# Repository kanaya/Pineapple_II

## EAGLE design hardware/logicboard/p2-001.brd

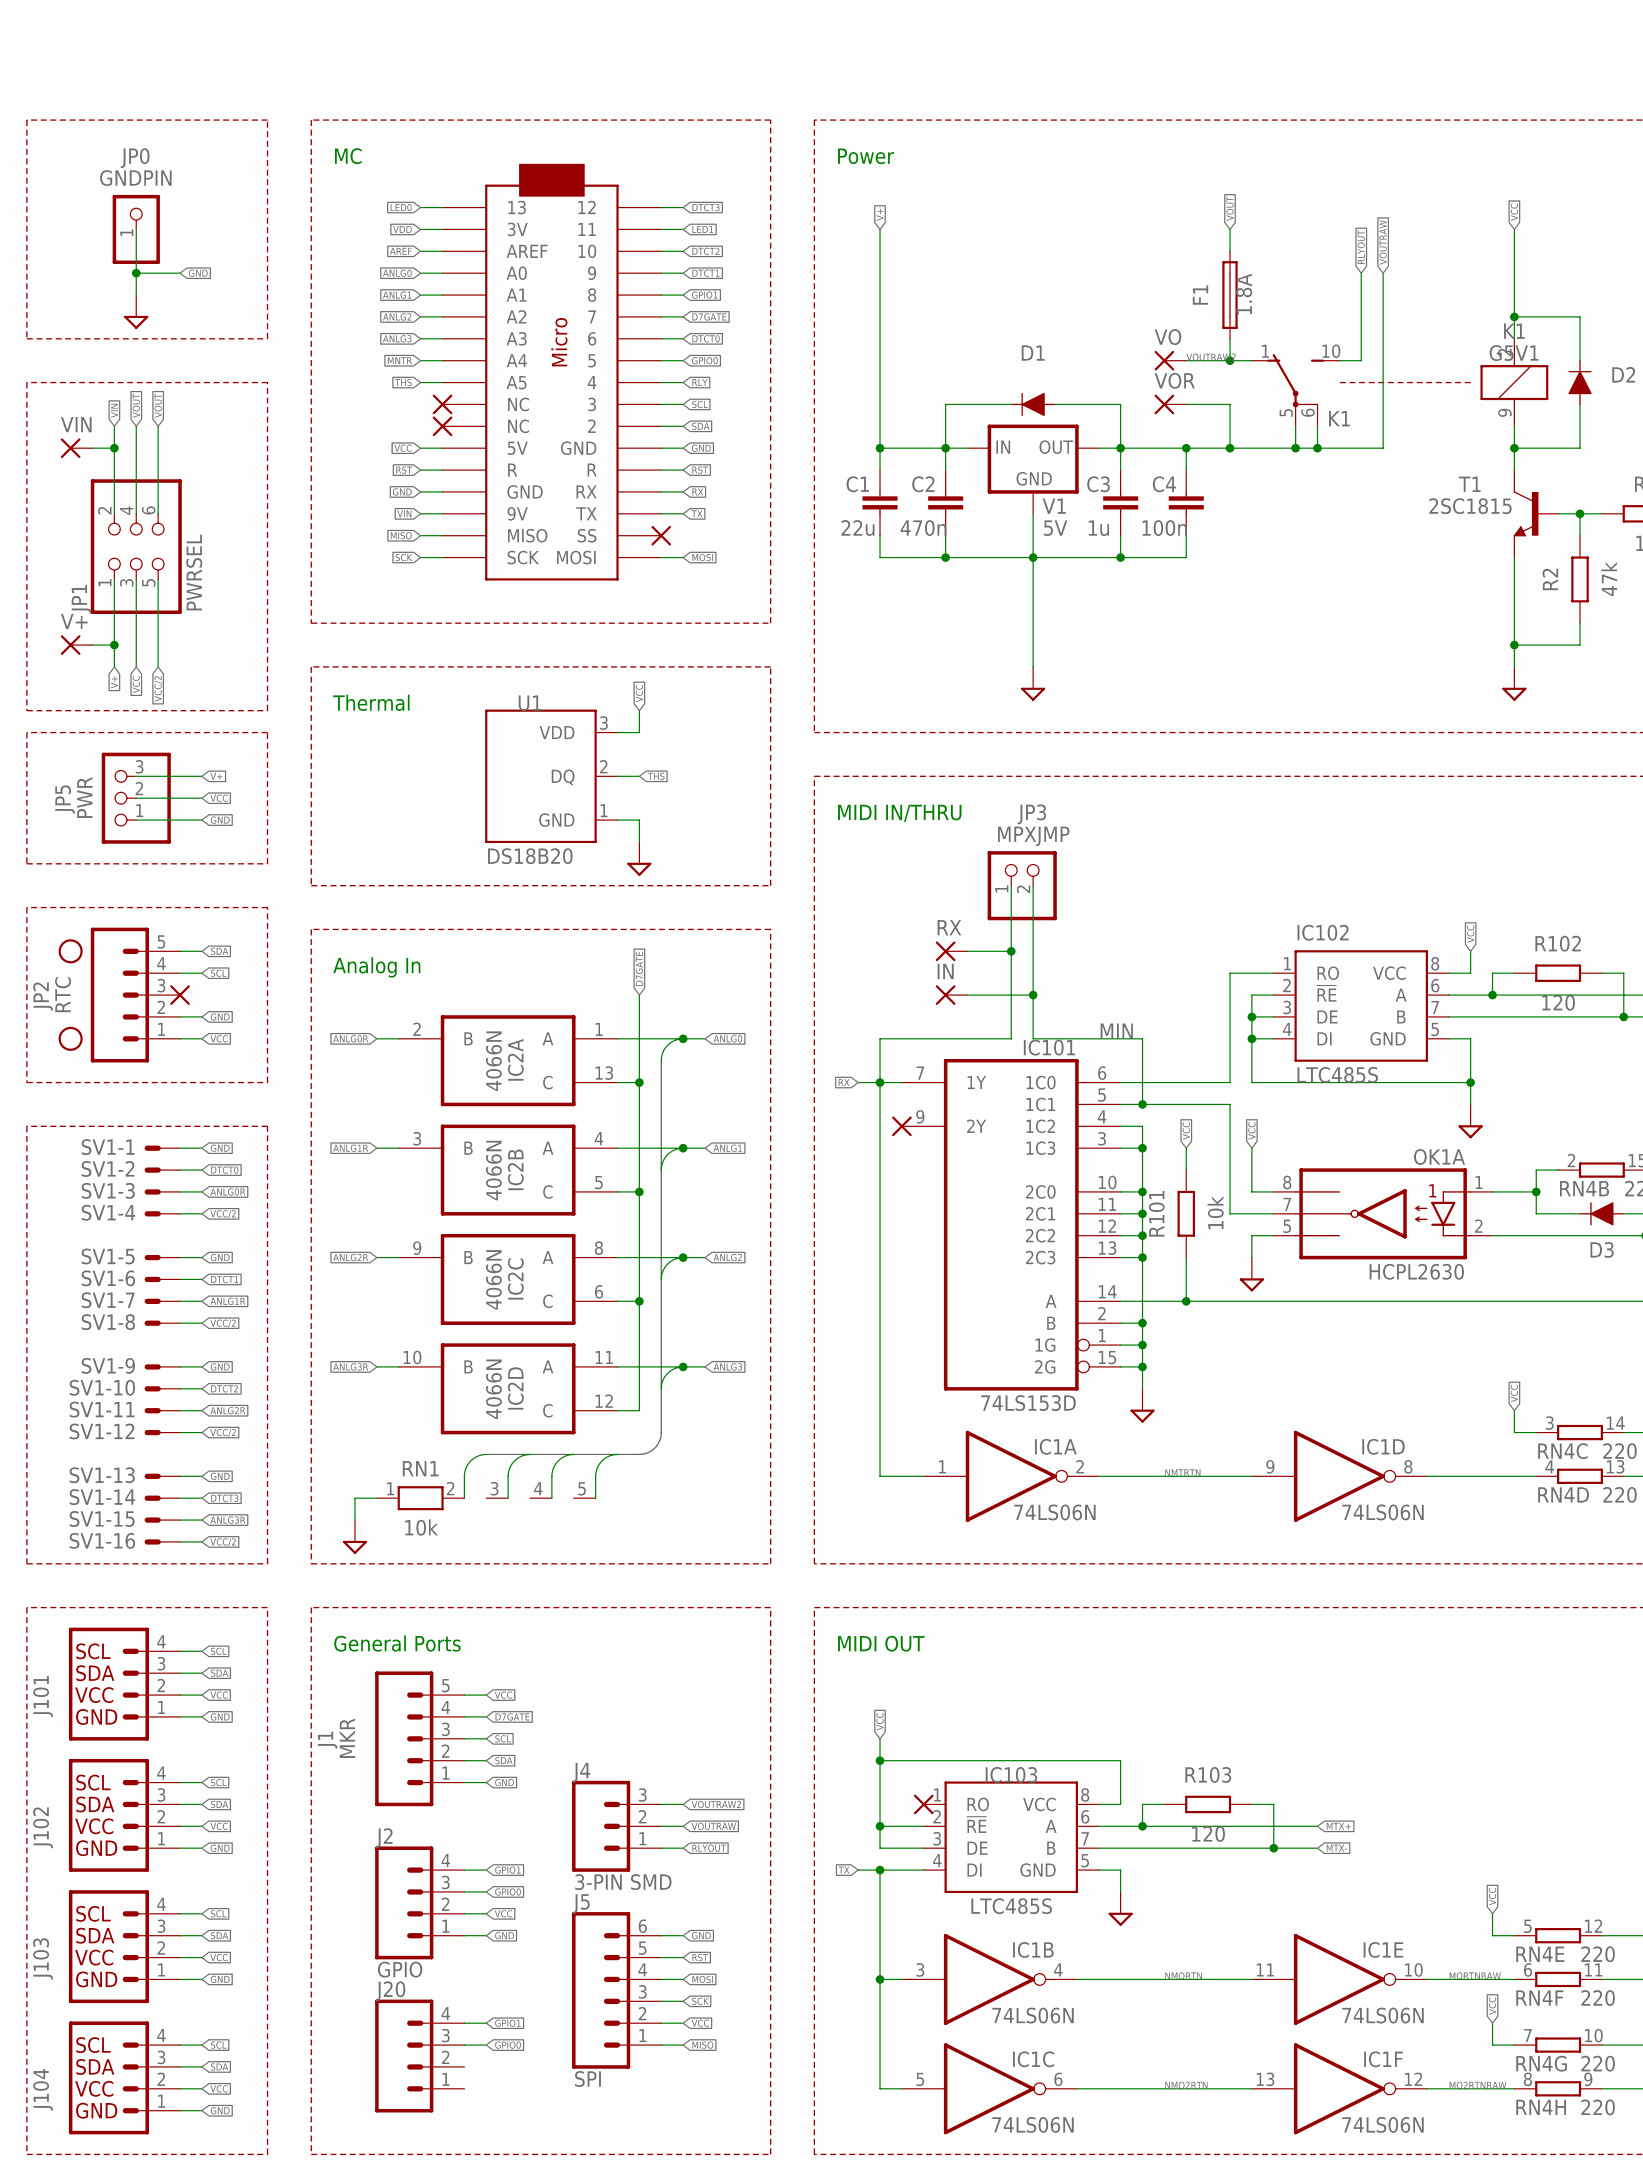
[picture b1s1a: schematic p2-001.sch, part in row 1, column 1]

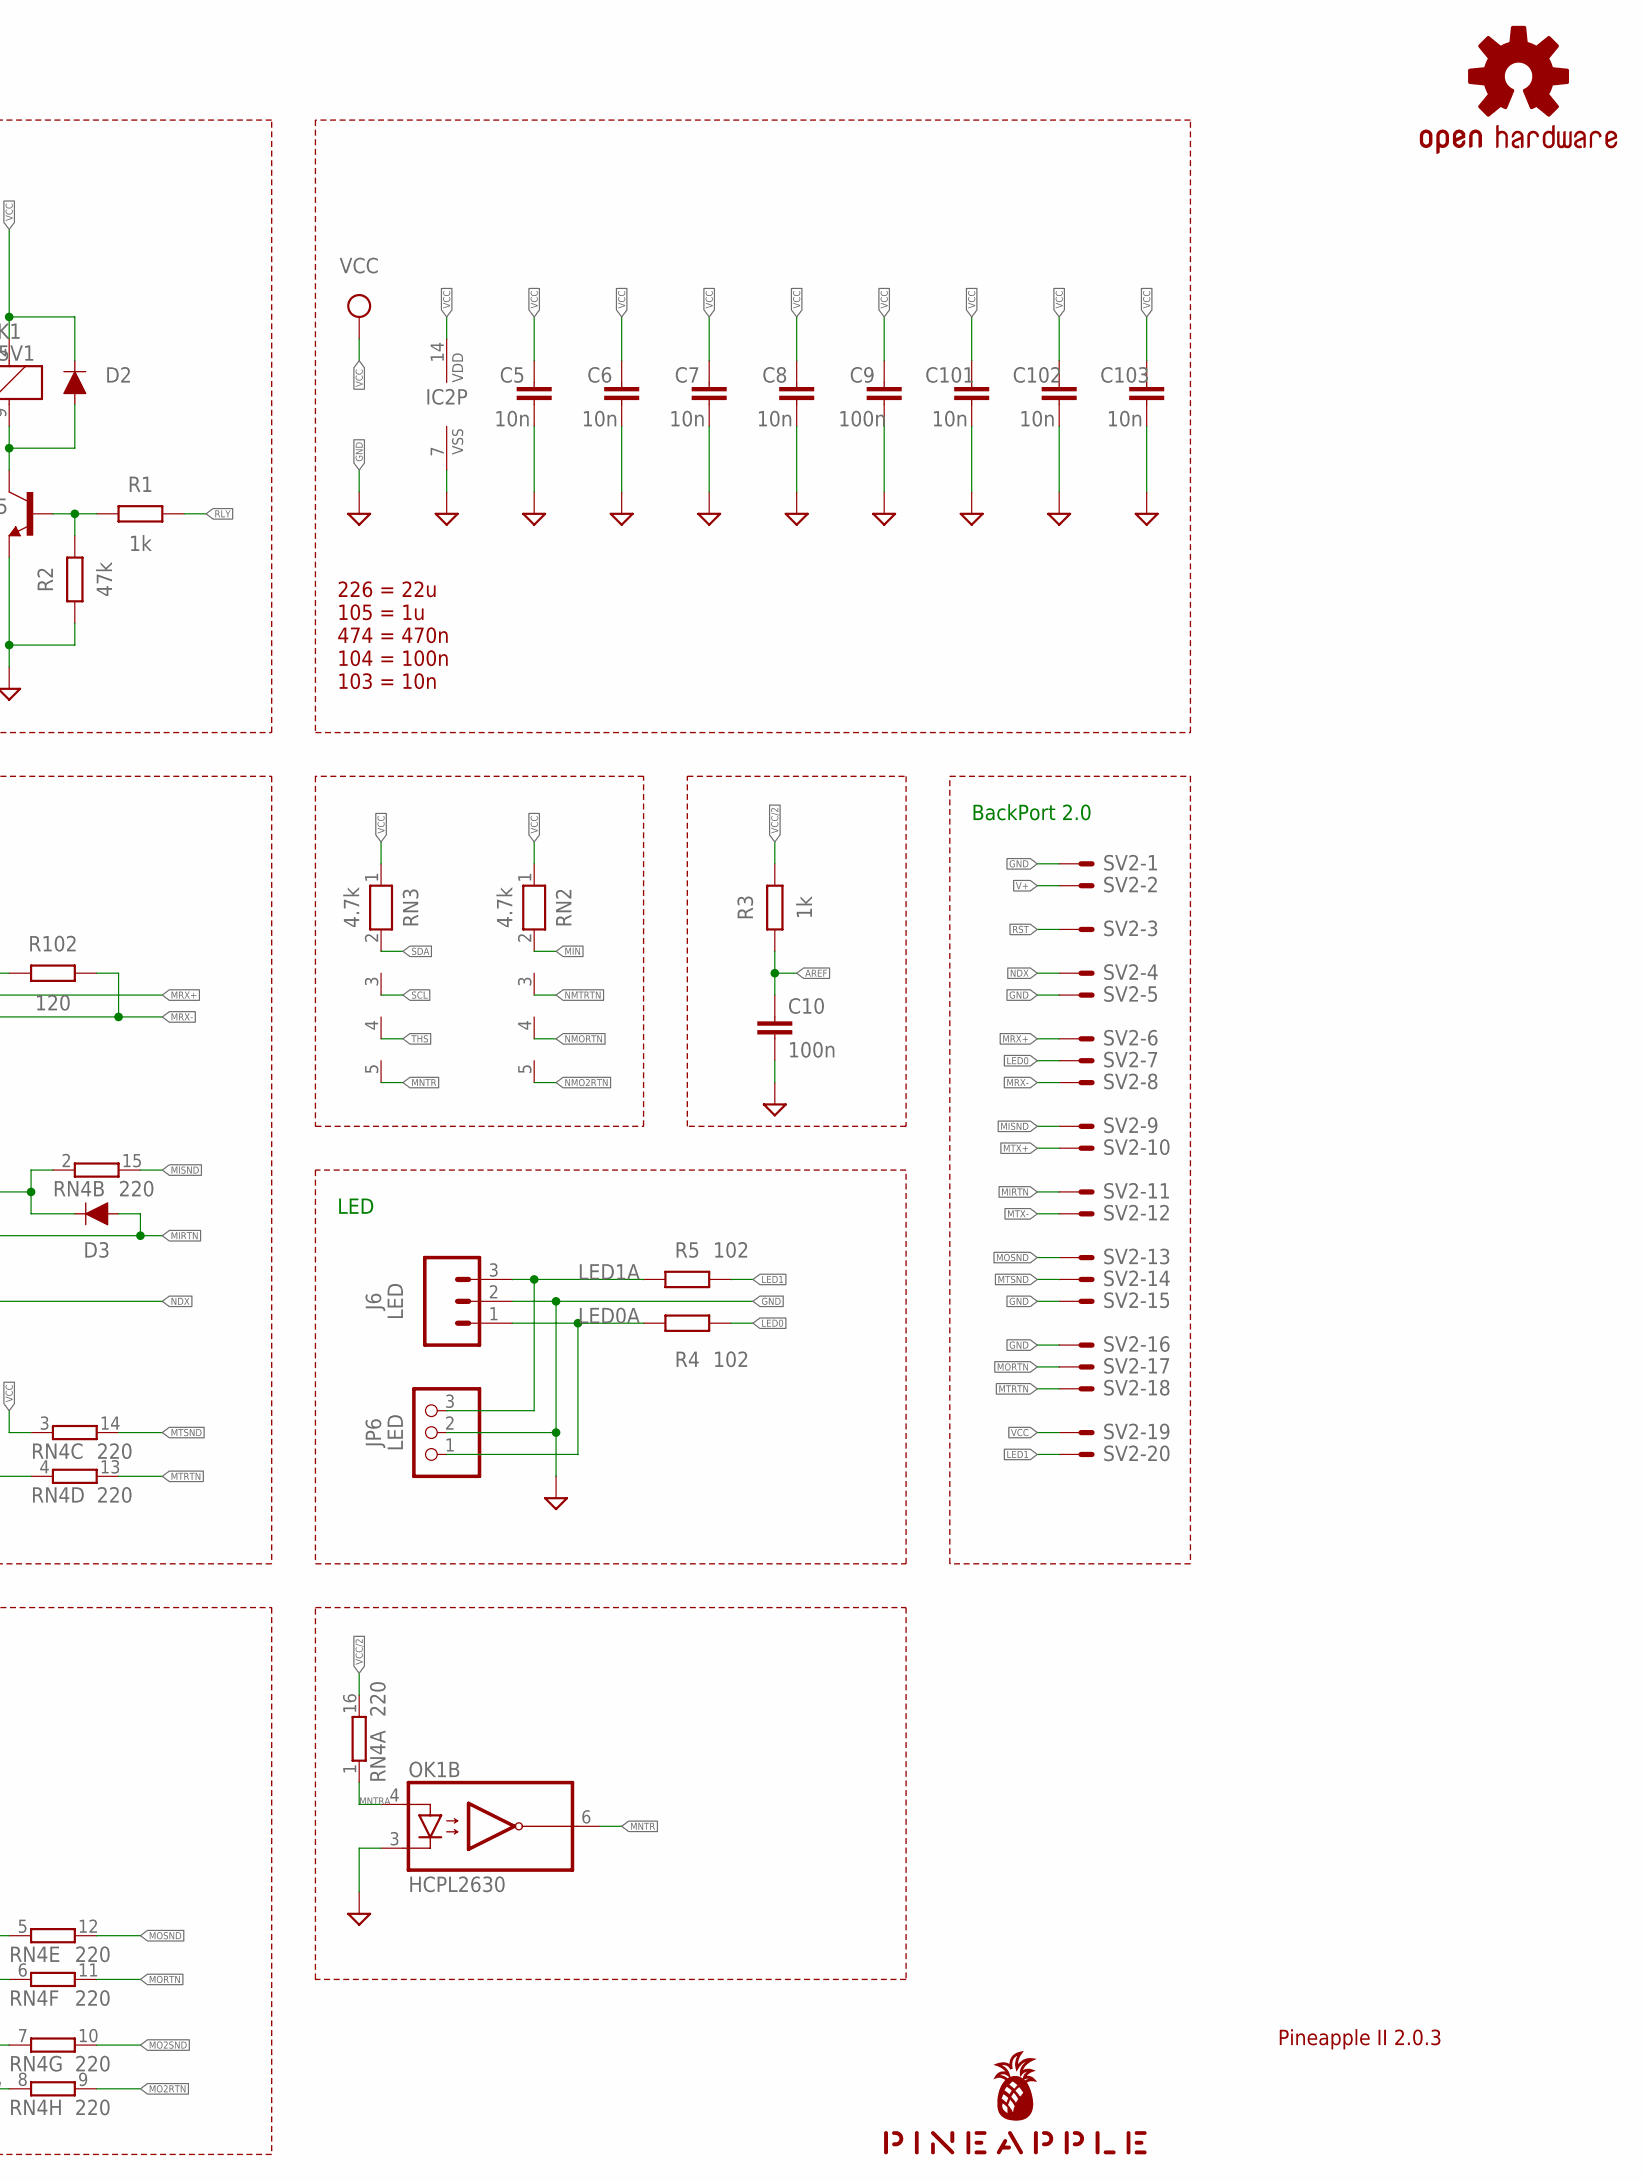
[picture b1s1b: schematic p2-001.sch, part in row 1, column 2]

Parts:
C1: 22u; C025-050X050
C2: 470n; C050-024X044
C3: 1u; C050-024X044
C4, C9, C10: 100n; C025-024X044
C5, C6, C7, C8: 10n; C025-024X044
C101, C102, C103: 10n; C2012
D1, D2, D3: DIODE-1N4148
F1: 1.8A; TE5
H1, H2: STAND-OFF
IC1: 74LS06N; DIL14
IC2: 4066N; DIL14
IC101: 74LS153D; SO16
IC102, IC103: LTC485S; SOIC8
IN: SMD2; SMD1,27-2,54
J1: MKR; JST-5-PTH
J2: GPIO; JST-4-PTH
J4: 3-PIN SMD; JST-3-SMD
J5: SPI; 1X06_1.27MM
J6: LED; JST-3-PTH
J20: CONN_041.27MM; 1X04_1.27MM
J101, J102, J103, J104: Qwiic; 1X04_1MM_RA
JP0: GNDPIN; 1X01
JP1: PWRSEL; 2X03
JP2: RTC; 1X05
JP3: MPXJMP; 1X02
JP5: PWR; 1X03
JP6: LED; 1X03
K1: G5V1
LOGO1: OSHW-LOGOS-COPPER; OSHW-LOGO-S_COPPER
MC1: ARDUINOMICRO
OK1: HCPL2630; DIL08
R1, R3: 1k; 0204/5
R2: 47k; 0204/5
R4, R5: 102; 0204/5
R101: 10k; M2012
R102, R103: 120; M2012
RN1: 10k; RN-5
RN2, RN3: 4.7k; RN-5
RN4: 220; DIL16
RX: SMD2; SMD1,27-2,54
SV1: ML16LE; ML16L
SV2: ML20LE; ML20L
T1: 2SC1815; TO92-ECB
U1: DS18B20; TO-92-AMMO
U$1: PINEAPPLE450_SILK
V1: 5V; 78XXL
V+: SMD2; SMD1,27-2,54
VIN: SMD2; SMD1,27-2,54
VO: SMD2; SMD1,27-2,54
VOR: SMD2; SMD1,27-2,54

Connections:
ANLG0: IC2.1 (A), MC1.P$31 (A0), RN1.2
ANLG0R: IC2.2 (B), SV1.3
ANLG1: IC2.4 (A), MC1.P$30 (A1), RN1.3
ANLG1R: IC2.3 (B), SV1.7
ANLG2: IC2.8 (A), MC1.P$29 (A2), RN1.4
ANLG2R: IC2.9 (B), SV1.11
ANLG3: IC2.11 (A), MC1.P$28 (A3), RN1.5
ANLG3R: IC2.10 (B), SV1.15
AREF: C10.1, MC1.P$32 (AREF), R3.1
D7GATE: IC2.5 (C), IC2.6 (C), IC2.12 (C), IC2.13 (C), J1.4, MC1.P$6 (7)
DTCT0: MC1.P$7 (6), SV1.2
DTCT1: MC1.P$4 (9), SV1.6
DTCT2: MC1.P$3 (10), SV1.10
DTCT3: MC1.P$1 (12), SV1.14
GND: C1.2, C2.2, C3.2, C4.2, C5.2, C6.2, C7.2, C8.2, C9.2, C10.2, C101.2, C102.2, C103.2, IC1.7 (GND), IC2.7 (VSS), IC101.1 (1G), IC101.2 (B), IC101.3 (1C3), IC101.4 (1C2), IC101.8 (GND), IC101.10 (2C0), IC101.11 (2C1), IC101.12 (2C2), IC101.13 (2C3), IC101.15 (2G), IC102.2 (!RE), IC102.3 (DE), IC102.4 (DI), IC102.5 (GND), IC103.5 (GND), J1.1, J2.1, J5.6, J6.2, J101.1 (GND), J102.1 (GND), J103.1 (GND), J104.1 (GND), JP0.1, JP2.2, JP5.1, JP6.2, MC1.P$12 (GND), MC1.P$21 (GND), OK1.3 (C2), OK1.5 (GND), R2.1, RN1.1, SV1.1, SV1.5, SV1.9, SV1.13, SV2.1, SV2.5, SV2.15, SV2.16, T1.E, U1.1 (GND), V1.GND
GPIO0: J2.3, J20.3, MC1.P$8 (5)
GPIO1: J2.4, J20.4, MC1.P$5 (8)
LED0: MC1.P$34 (13), R4.2, SV2.7
LED0A: J6.1, JP6.1, R4.1
LED1: MC1.P$2 (11), R5.2, SV2.20
LED1A: J6.3, JP6.3, R5.1
MIDIINSND: D3.C, OK1.1 (A1), RN4.2 (1)
MIN: IC101.5 (1C1), IN.1, JP3.2, OK1.7 (VO1), RN2.2
MIRTN: D3.A, OK1.2 (C1), SV2.11
MISND: RN4.15 (2), SV2.9
MISO: J5.1, MC1.P$19 (MISO)
MNTR: MC1.P$27 (A4), OK1.6 (VO2), RN3.5
MNTRA: OK1.4 (A2), RN4.1
MO2RTN: RN4.9 (2)
MO2RTNRAW: IC1.12 (O), RN4.8 (1)
MO2SND: RN4.10 (2)
MORTN: RN4.11 (2), SV2.17
MORTNRAW: IC1.10 (O), RN4.6 (1)
MOSI: J5.4, MC1.P$17 (MOSI)
MOSND: RN4.12 (2), SV2.13
MRX: IC101.6 (1C0), IC102.1 (RO)
MRX+: IC102.6 (A), R102.1, SV2.6
MRX-: IC102.7 (B), R102.2, SV2.8
MTRTN: RN4.13 (2), SV2.18
MTRTNRAW: IC1.8 (O), RN4.4 (1)
MTSND: RN4.14 (2), SV2.14
MTX+: IC103.6 (A), R103.1, SV2.10
MTX-: IC103.7 (B), R103.2, SV2.12
NDX: IC101.14 (A), R101.1, SV2.4
NMO2RTN: IC1.6 (O), IC1.13 (I), RN2.5
NMORTN: IC1.4 (O), IC1.11 (I), RN2.4
NMTRTN: IC1.2 (O), IC1.9 (I), RN2.3
RLY: MC1.P$9 (4), R1.2
RLYDRV: R1.1, R2.2, T1.B
RLYSNK: D2.A, K1.9 (2), T1.C
RST: J5.5, MC1.P$13 (R), MC1.P$22 (R), SV2.3
RX: IC1.1 (I), IC101.7 (1Y), JP3.1, MC1.P$14 (RX), RX.1
SCK: J5.3, MC1.P$18 (SCK)
SCL: J1.3, J101.4 (SCL), J102.4 (SCL), J103.4 (SCL), J104.4 (SCL), JP2.4, MC1.P$10 (3), RN3.3
SDA: J1.2, J101.3 (SDA), J102.3 (SDA), J103.3 (SDA), J104.3 (SDA), JP2.5, MC1.P$11 (2), RN3.2
THS: MC1.P$26 (A5), RN3.4, U1.2 (DQ)
TX: IC1.3 (I), IC1.5 (I), IC103.4 (DI), MC1.P$15 (TX)
V+: C1.1, C2.1, D1.C, JP1.1, JP5.3, SV2.2, V1.IN, V+.1
VCC: C5.1, C6.1, C7.1, C8.1, C9.1, C101.1, C102.1, C103.1, D2.C, IC1.14 (VCC), IC2.14 (VDD), IC101.16 (VCC), IC102.8 (VCC), IC103.2 (!RE), IC103.3 (DE), IC103.8 (VCC), J1.5, J2.2, J5.2, J101.2 (VCC), J102.2 (VCC), J103.2 (VCC), J104.2 (VCC), JP1.3, JP2.1, JP5.2, K1.2 (1), MC1.P$23 (5V), OK1.8 (VCC), R101.2, RN2.1, RN3.1, RN4.3 (1), RN4.5 (1), RN4.7 (1), SV2.19, U1.3 (VDD)
VCC/2: JP1.5, R3.2, RN4.16 (2), SV1.4, SV1.8, SV1.12, SV1.16
VDD: MC1.P$33 (3V)
VIN: JP1.2, MC1.P$20 (9V), VIN.1
VOUT: F1.2, JP1.4, JP1.6
VOUTRAW: C3.1, C4.1, D1.A, J4.2, K1.5, K1.6, V1.OUT, VOR.1

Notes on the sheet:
Pineapple II 2.0.3
226 = 22u 105 = 1u 474 = 470n 104 = 100n 103 = 10n
MIDI IN/THRU
MIDI OUT
Power
General Ports
Analog In
Thermal
LED
BackPort 2.0

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
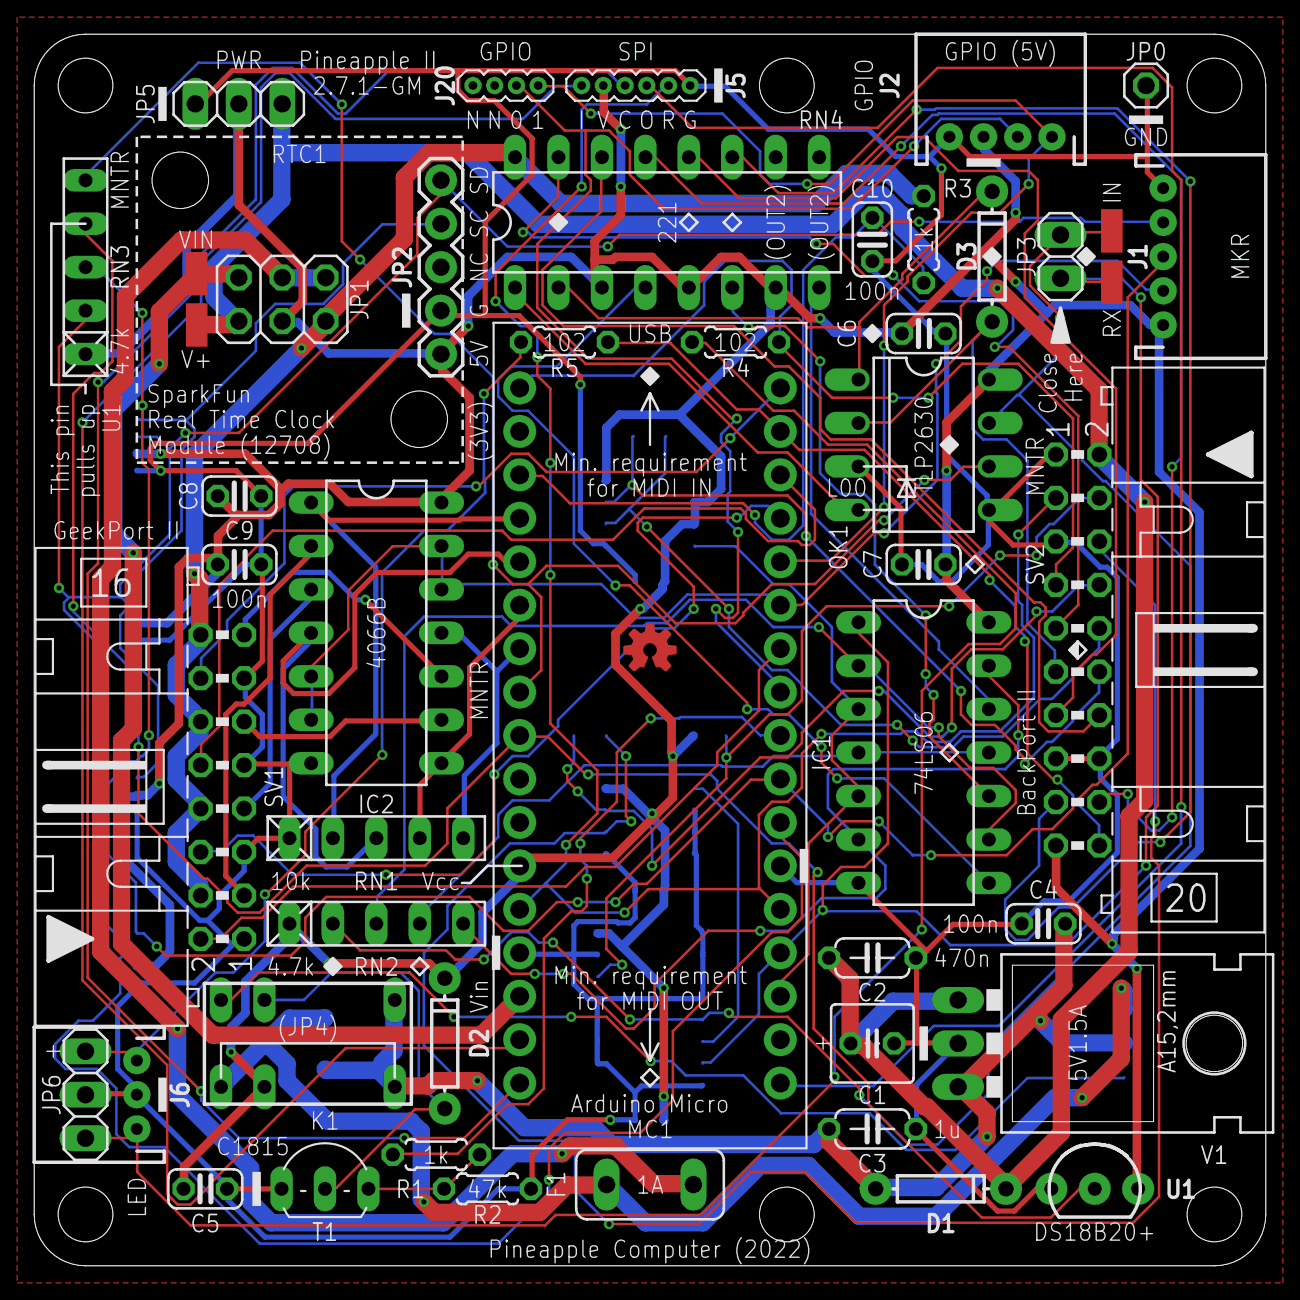
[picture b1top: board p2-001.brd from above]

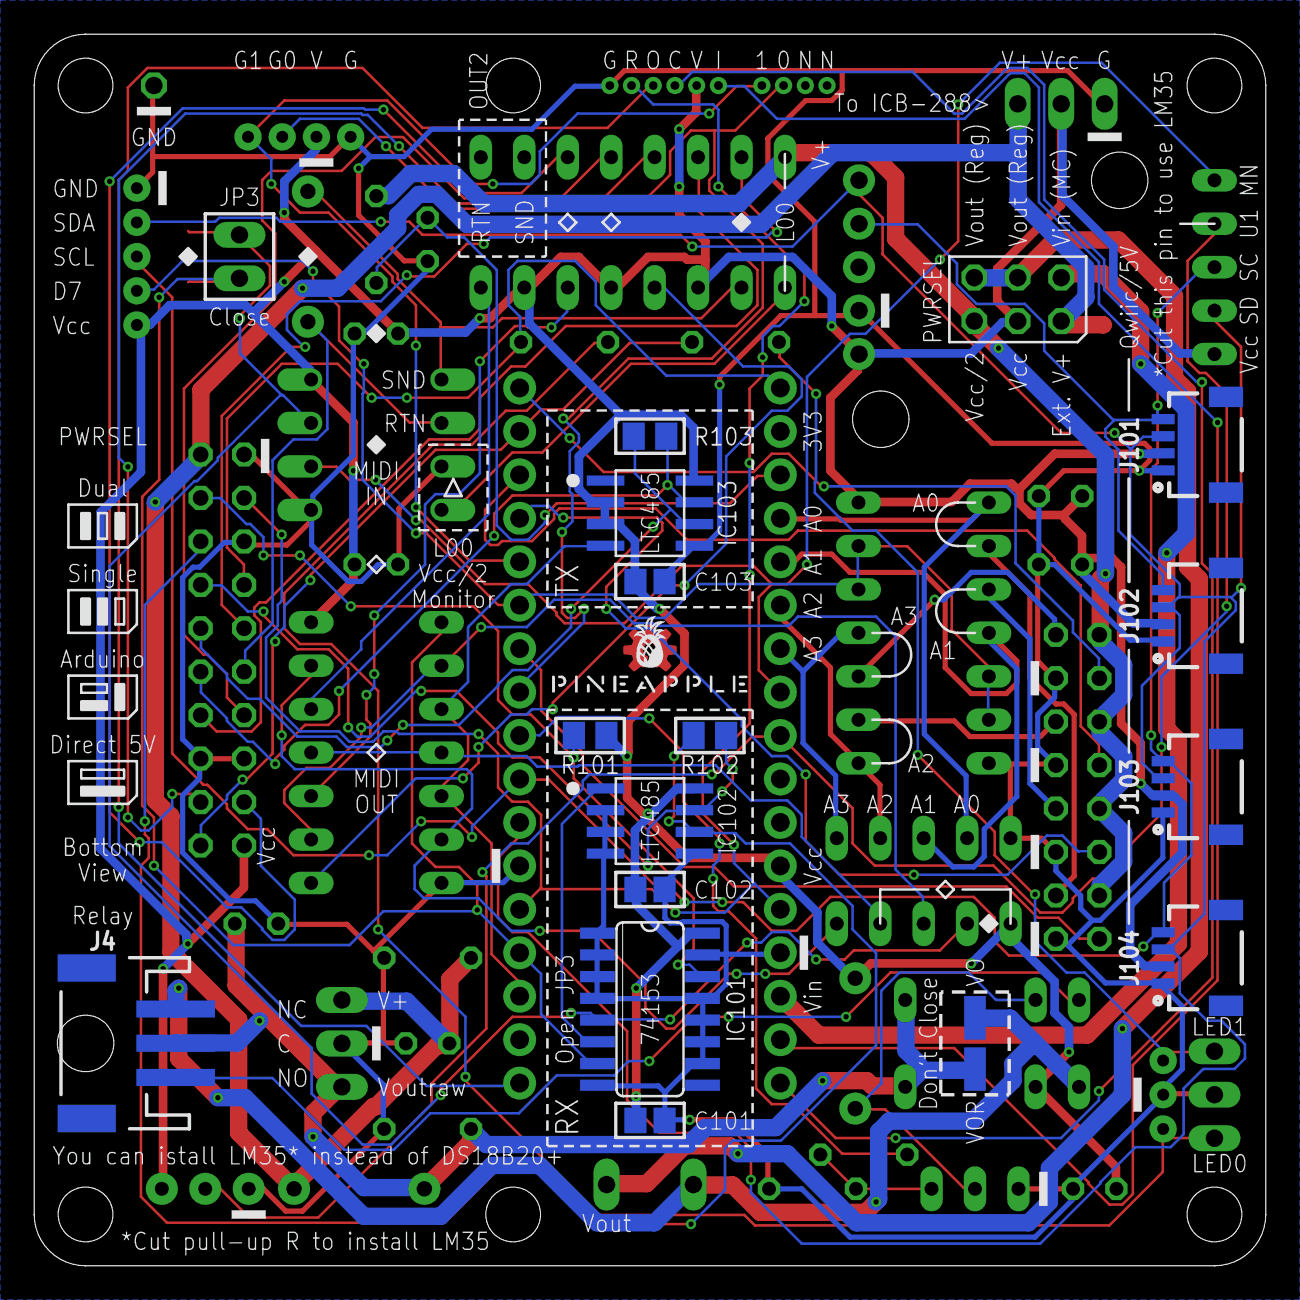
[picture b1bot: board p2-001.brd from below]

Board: 2 copper layers, 72.0 x 72.0 mm, 68 parts (17 on the bottom side), 63 nets.

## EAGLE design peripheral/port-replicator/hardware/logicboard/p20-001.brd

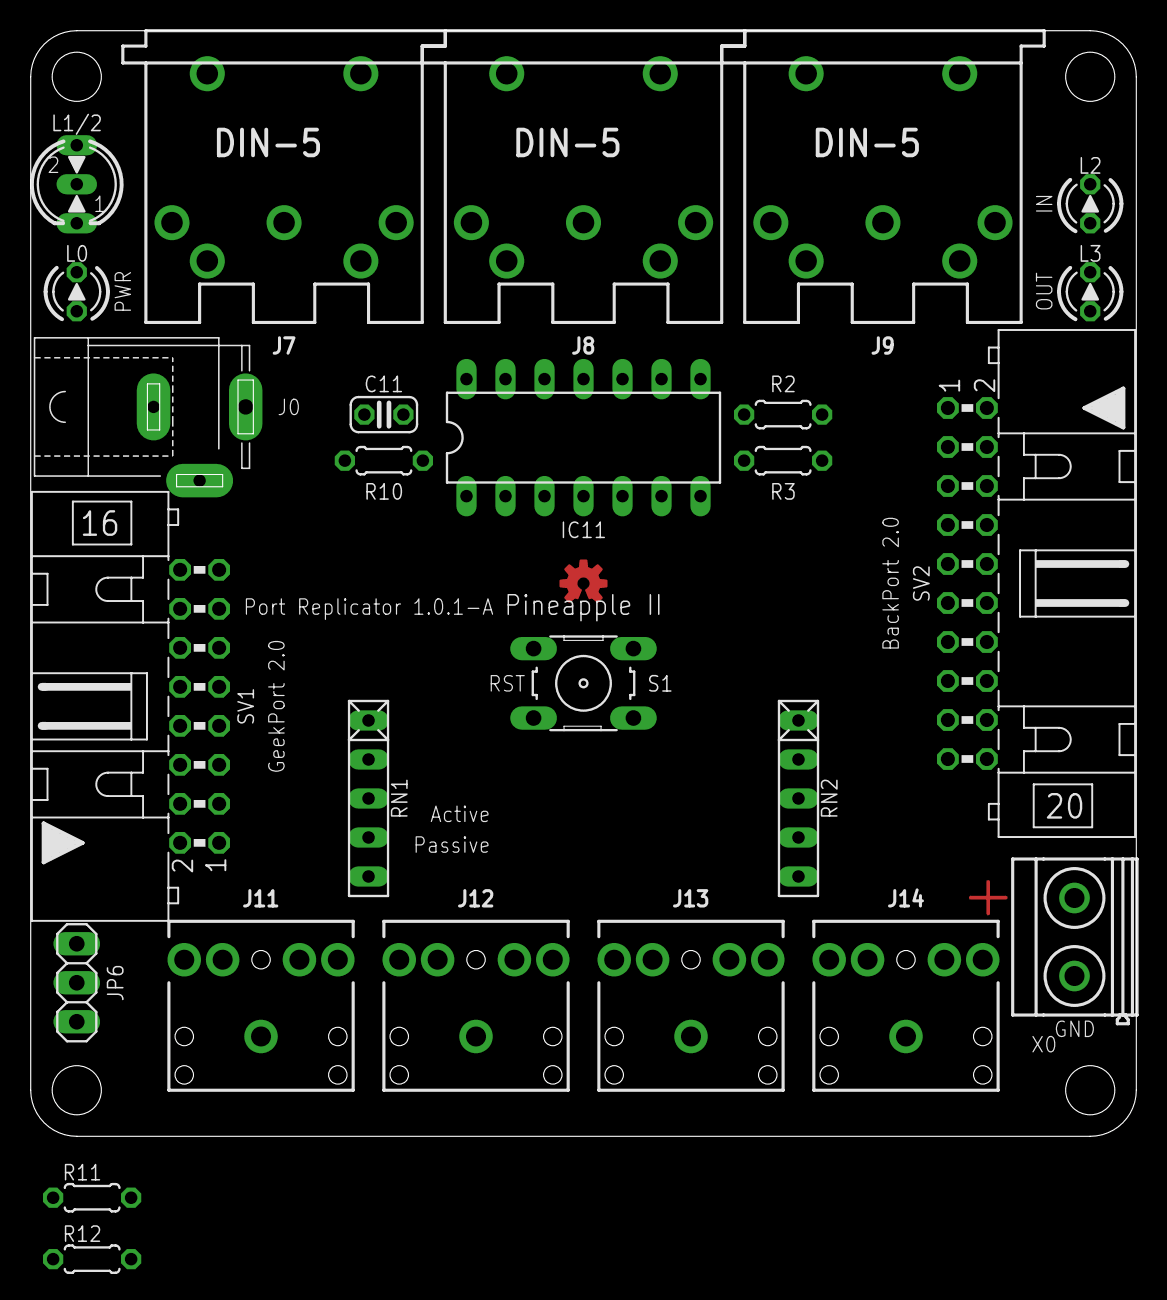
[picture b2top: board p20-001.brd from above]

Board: 2 copper layers, 72.0 x 72.0 mm, 28 parts (1 on the bottom side), 28 nets, no tracks yet.

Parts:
C11: 10n; C025-024X044
IC11: 74ALS04N; DIL14
J0: DC9V; SPC4077
J7, J8, J9: DIN5; DIN5-RA-PTH
J11, J12, J13, J14: AUDIO_JACK_3.5MM_PTH; AUDIO-JACK
JP6: 1X03
L0: PWR; LED3MM
L1/2: DUOLED-C-5MM
L2: IN; LED3MM
L3: OUT; LED3MM
LOGO1: OSHW-LOGOS-COPPER; OSHW-LOGO-S_COPPER
R2, R3, R10, R11, R12: 0204/5
RN1, RN2: RN-5
S1: B3F-10XX
SV1: ML16L
SV2: ML20L
U$1: PINEAPPLE450_SILK
X0: MKDSN1,5/2-5,08

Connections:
ANLG1R: J11.RING, SV1.4
ANLG2R: J12.RING, SV1.8
ANLG3R: J13.RING, SV1.12
ANLG4R: J14.RING, SV1.16
DTCT1: J11.TSH, RN1.2, SV1.3
DTCT2: J12.TSH, RN1.3, SV1.7
DTCT3: J13.TSH, RN1.4, SV1.11
DTCT4: J14.TSH, RN1.5, SV1.15
GND: C11.2, IC11.7, J0.1, J0.2, J8.2, J9.2, J11.SLEEVE, J12.SLEEVE, J13.SLEEVE, J14.SLEEVE, JP6.2, L0.K, L1/2.C, RN1.1, S1.1, S1.2, SV1.1, SV1.5, SV1.9, SV1.13, SV2.1, SV2.10, SV2.11, SV2.13, X0.1
LED1: JP6.1, R11.2, SV2.9
LED2: JP6.3, R12.1, SV2.17
LEDMI: L2.K, R2.2
LEDMO: L3.K, R3.2
LEDPWR: L0.A, R10.1
MIRTN: IC11.1, J7.5, SV2.5
MISND: J7.4, SV2.4
MORTN: J9.5, SV2.15
MOSND: IC11.3, J9.4, SV2.14
MTRTN: J8.5, SV2.20
MTSND: J8.4, SV2.19
unnamed: IC11.2, R2.1
unnamed: IC11.4, R3.1
unnamed: L1/2.AR, R11.1
unnamed: L1/2.AX, R12.2
RST: S1.3, S1.4, SV2.3
V+: J0.3, SV2.2, X0.2
VCC: C11.1, IC11.14, L2.A, L3.A, SV2.12
VCC/2: J11.TIP, J12.TIP, J13.TIP, J14.TIP, R10.2, SV1.2, SV1.6, SV1.10, SV1.14

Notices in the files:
parts and their libraries:
SparkFun-DiscreteSemi: Licensing: Creative Commons ShareAlike 4.0 International - https://creativecommons.org/licenses/by-sa/4.0
